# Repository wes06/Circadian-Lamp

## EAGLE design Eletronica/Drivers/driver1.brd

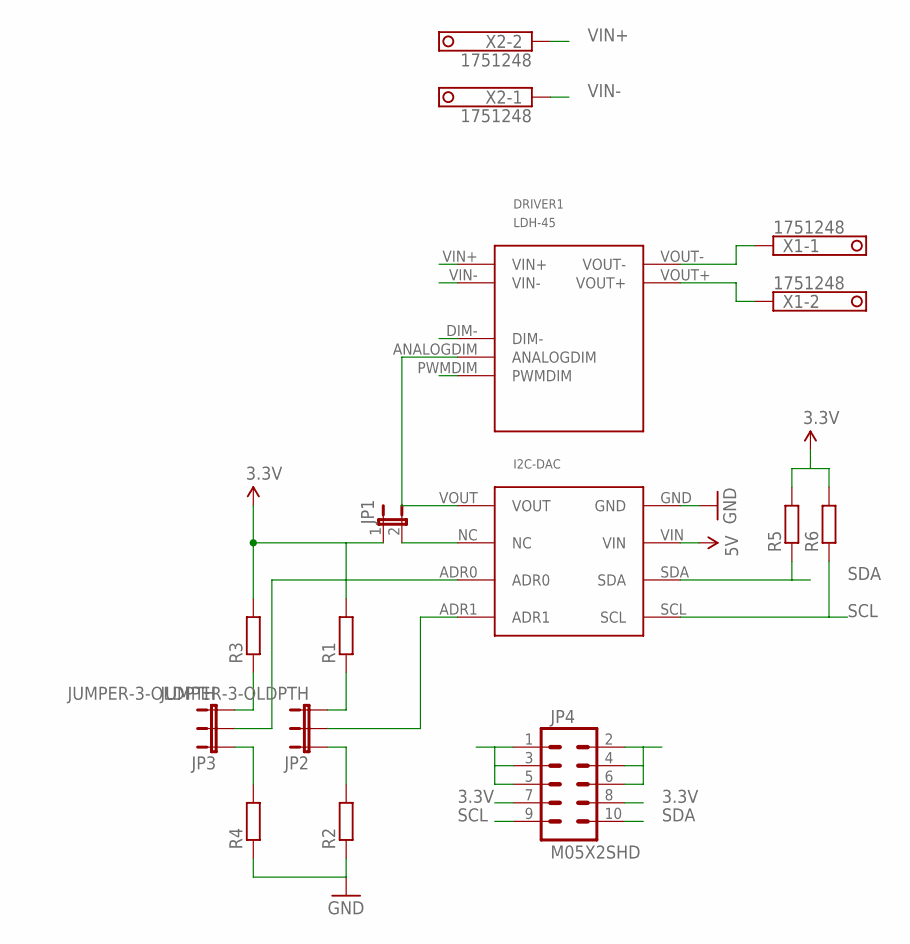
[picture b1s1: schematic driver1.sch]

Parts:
DRIVER1: LDH-45
JP1: JUMPER-2PTH_LOCK; 1X02_LOCK
JP2, JP3: JUMPER-3-OLDPTH; 1X03
JP4: M05X2SHD; 2X5-SHROUDED
R1, R2, R3, R4, R5, R6: R-EU_R0603; R0603
U$1: I2C-DAC
X1, X2: 1751248

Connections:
3.3V: JP1.1, JP4.7, JP4.8, R1.2, R3.2, R5.2, R6.2
5V: JP4.2, JP4.4, JP4.6, U$1.VIN
GND: JP4.1, JP4.3, JP4.5, R2.1, R4.1, U$1.GND
unnamed: DRIVER1.VOUT-, X1.1
unnamed: DRIVER1.VOUT+, X1.2
unnamed: DRIVER1.ANALOGDIM, U$1.VOUT
unnamed: JP3.2, U$1.ADR0
unnamed: JP3.3, R3.1
unnamed: JP1.2, U$1.NC
unnamed: JP3.1, R4.2
unnamed: JP2.3, R1.1
unnamed: JP2.1, R2.2
unnamed: JP2.2, U$1.ADR1
SCL: JP4.9, R6.1, U$1.SCL
SDA: JP4.10, R5.1, U$1.SDA
VIN+: DRIVER1.VIN+, X2.2
VIN-: DRIVER1.VIN-, X2.1

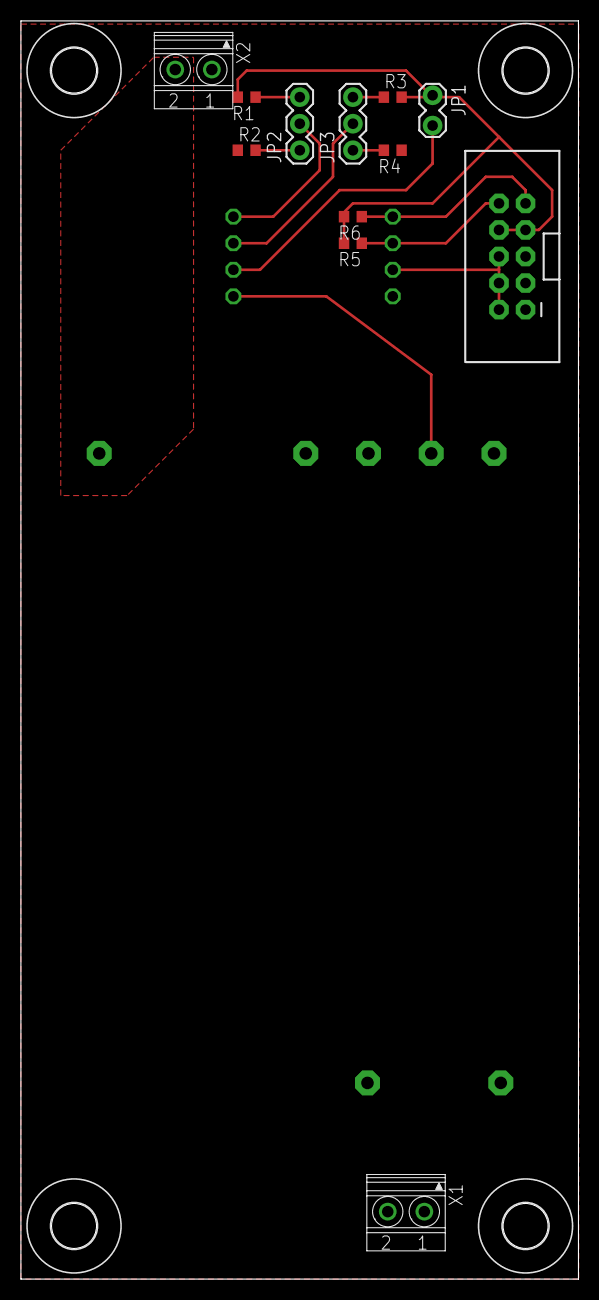
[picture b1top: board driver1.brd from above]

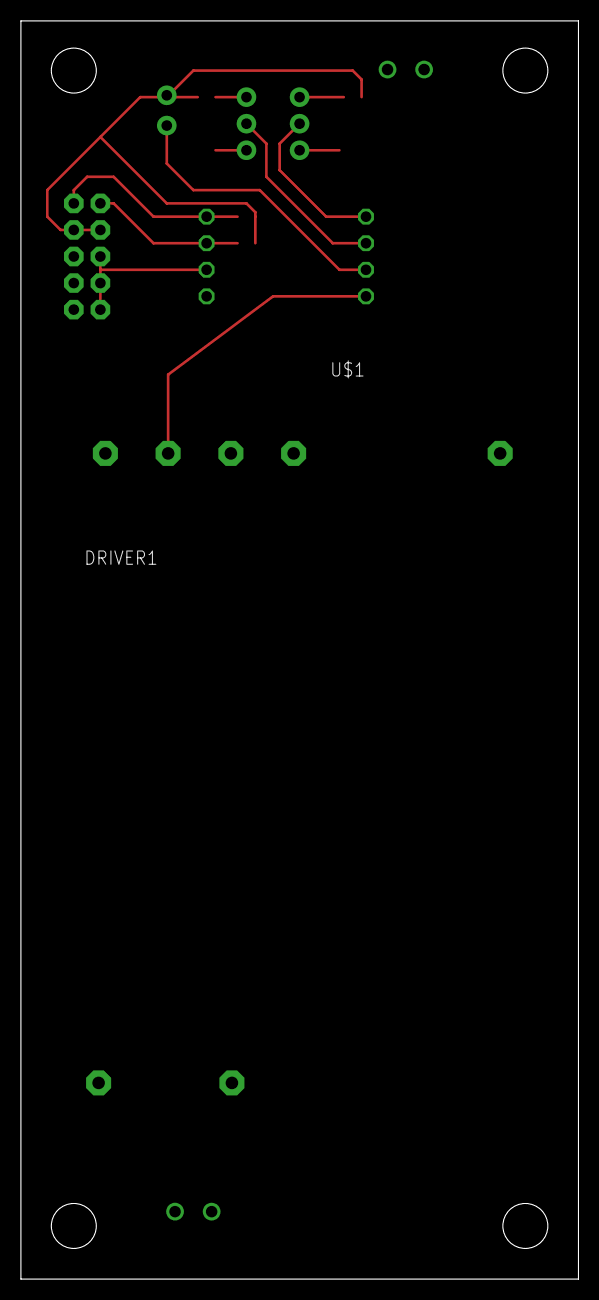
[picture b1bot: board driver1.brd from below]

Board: 2 copper layers, 53.3 x 120.3 mm, 18 parts (2 on the bottom side), 17 nets.

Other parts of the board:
U$2, U$3, U$4, U$5: 4,3

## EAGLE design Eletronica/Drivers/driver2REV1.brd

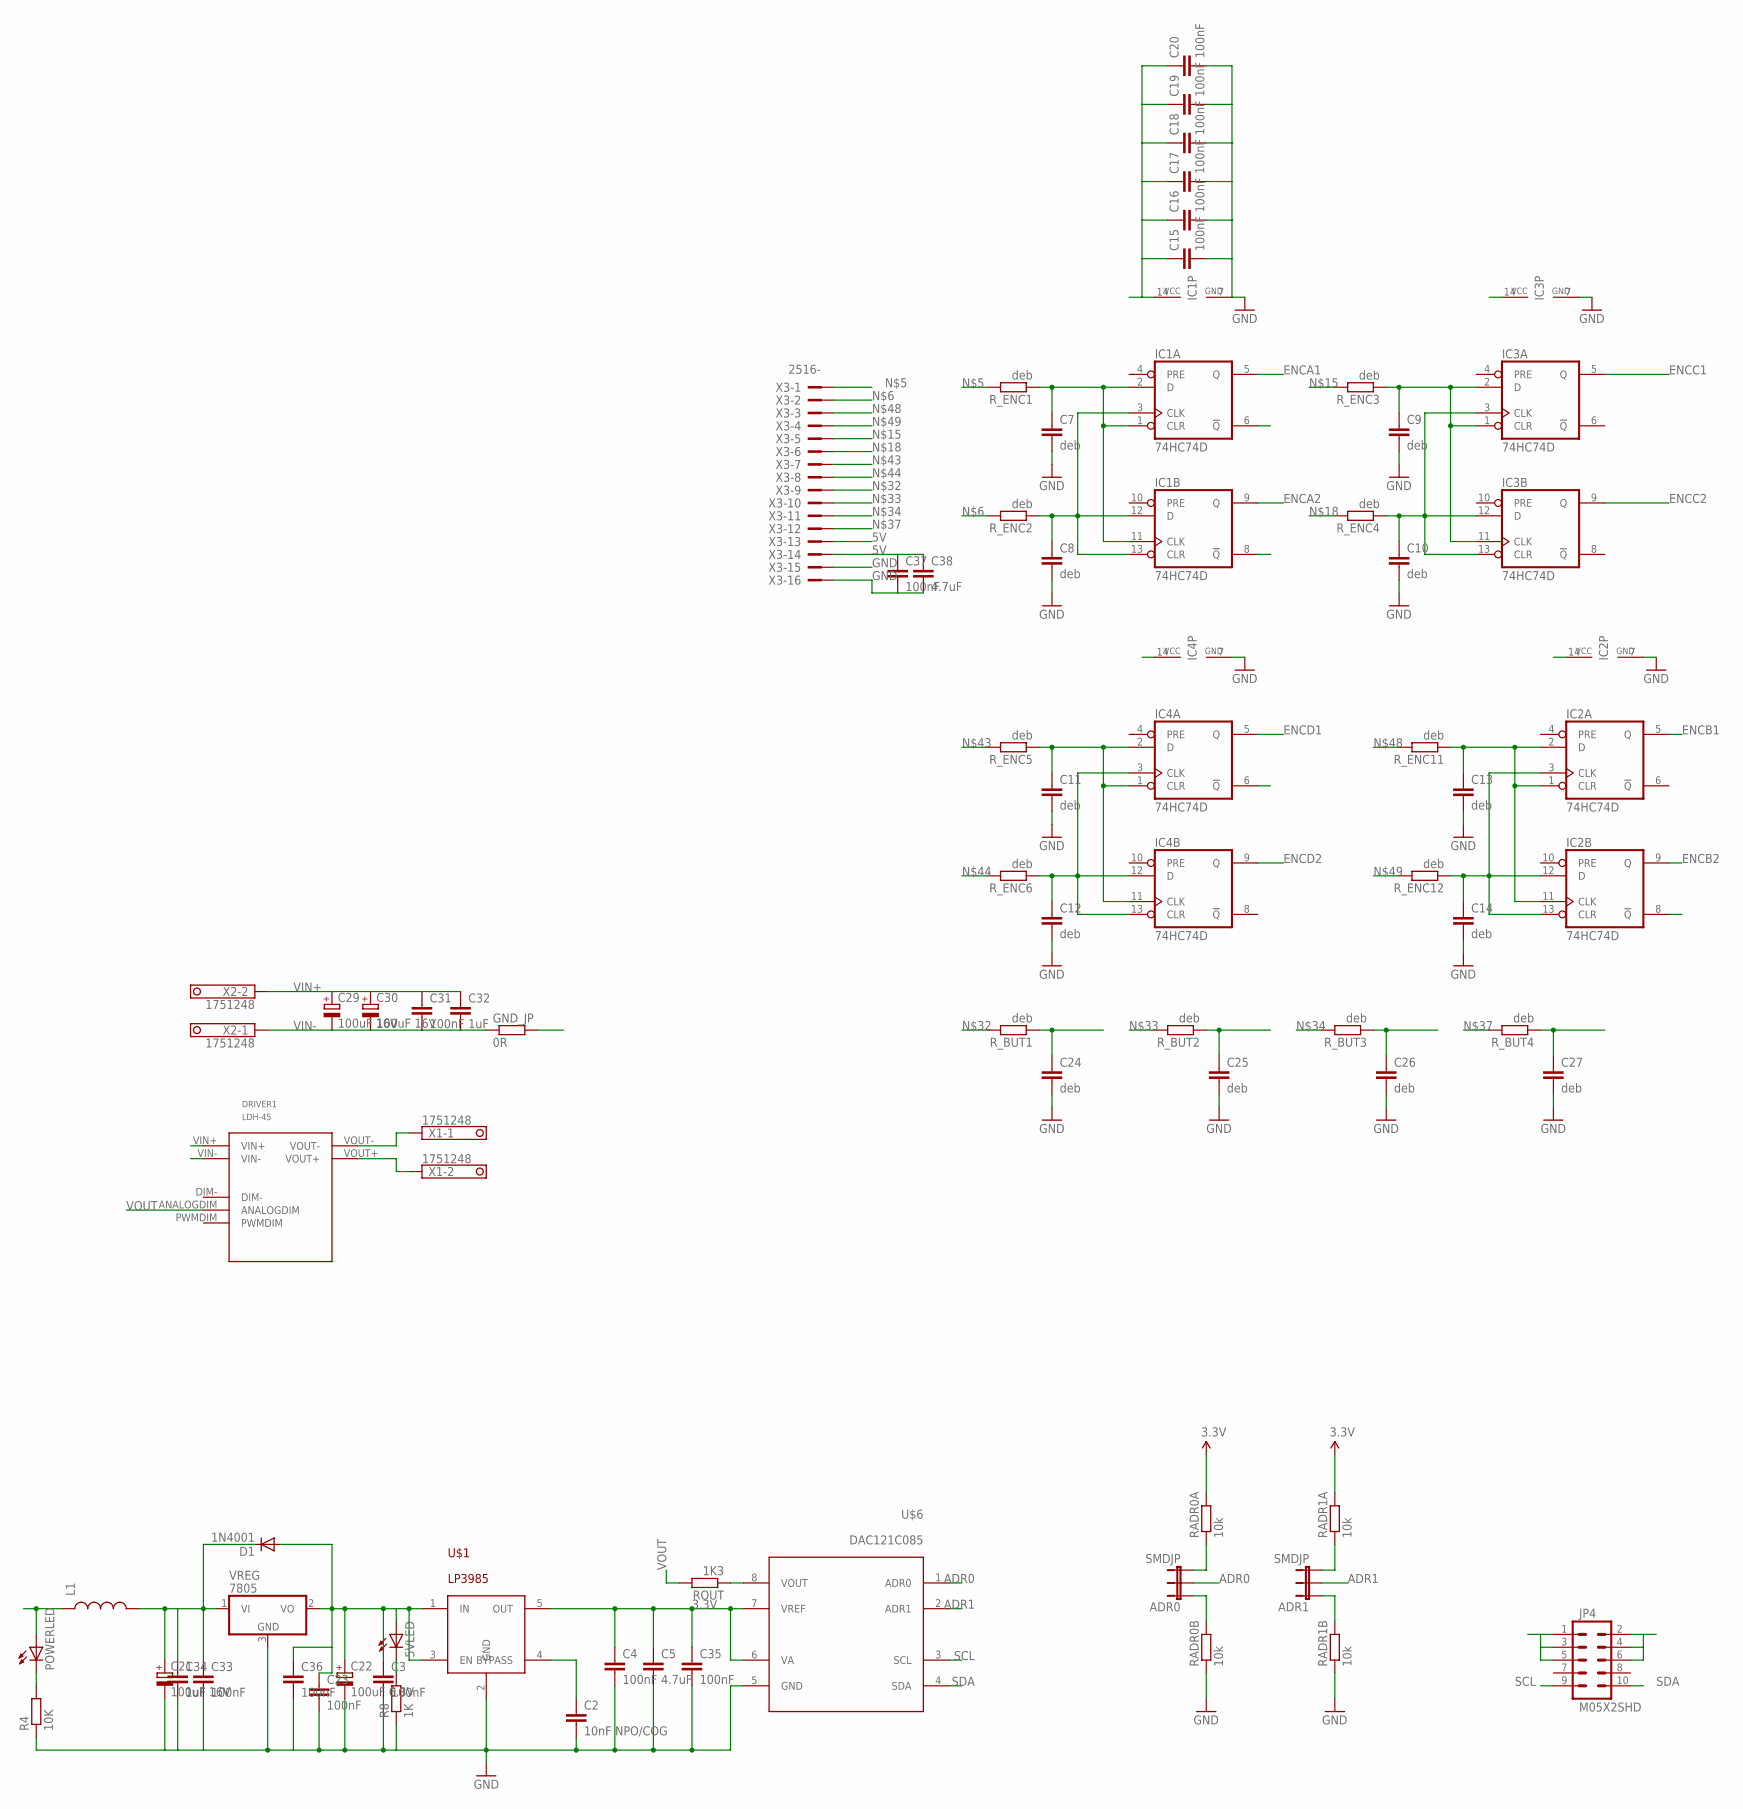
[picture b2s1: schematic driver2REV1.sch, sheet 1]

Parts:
5VLED: LEDCHIP-LED0805; CHIP-LED0805
ADR0, ADR1: SMDJP; SJ_3
C2: 10nF NPO/COG; C0805
C3, C4, C15, C16, C17, C18, C19, C20, C23, C31, C33, C35, C36, C37: 100nF; C0805
C5, C38: 4.7uF; C0805
C7, C8, C9, C10, C11, C12, C13, C14, C24, C25, C26, C27: deb; C0805
C21, C29, C30: 100uF 16V; UD-6,3X5,8_NICHICON
C22: 100uF 6.3V; UD-6,3X5,8_NICHICON
C32, C34: 1uF; C0805
D1: 1N4001; SMB-DIODE
DRIVER1: LDH-45
GND_JP: 0R; R1210
IC1, IC2, IC3, IC4: 74HC74D; SO14
JP4: M05X2SHD; 2X5-SHROUDED
L1: INDUCTOR0805; 0805
POWERLED: LEDCHIP-LED0805; CHIP-LED0805
R4: 10K; R0805
R8: 1K; R0805
RADR0A, RADR0B, RADR1A, RADR1B: 10k; R0603
ROUT: 1K3; R0603
R_BUT1, R_BUT2, R_BUT3, R_BUT4: deb; R0603
R_ENC1, R_ENC2, R_ENC3, R_ENC4, R_ENC5, R_ENC6, R_ENC11, R_ENC12: deb; R0603
U$1: LP3985; SOT23-5
U$6: DAC121C085; VSSOP-8
VREG: 7805; TO252
X1, X2: 1751248
X3: 2516-; PAK100/2500-16

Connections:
3.3V: C4.1, C5.1, C35.1, RADR0A.2, RADR1A.2, U$1.5 (OUT), U$6.6 (VA), U$6.7 (VREF); also elsewhere on the board
5V: 5VLED.A, C3.1, C15.1, C16.1, C17.1, C18.1, C19.1, C20.1, C22.+, C23.1, C36.1, C37.1, C38.1, D1.A, IC1.14 (VCC), IC2.14 (VCC), IC3.14 (VCC), IC4.14 (VCC), JP4.2, JP4.4, JP4.6, U$1.1 (IN), U$1.3 (EN), VREG.2 (VO), X3.13, X3.14; also elsewhere on the board
ADR0: ADR0.2, U$6.1 (ADR0)
ADR1: ADR1.2, U$6.2 (ADR1)
BUTA: C24.1, R_BUT1.1; also elsewhere on the board
BUTB: C25.1, R_BUT2.1; also elsewhere on the board
BUTC: C26.1, R_BUT3.1; also elsewhere on the board
BUTD: C27.1, R_BUT4.1; also elsewhere on the board
ENCA1: IC1.5 (Q); also elsewhere on the board
ENCA2: IC1.9 (Q); also elsewhere on the board
ENCB1: IC2.5 (Q); also elsewhere on the board
ENCB2: IC2.9 (Q); also elsewhere on the board
ENCC1: IC3.5 (Q); also elsewhere on the board
ENCC2: IC3.9 (Q); also elsewhere on the board
ENCD1: IC4.5 (Q); also elsewhere on the board
ENCD2: IC4.9 (Q); also elsewhere on the board
GND: C2.2, C3.2, C4.2, C5.2, C7.2, C8.2, C9.2, C10.2, C11.2, C12.2, C13.2, C14.2, C15.2, C16.2, C17.2, C18.2, C19.2, C20.2, C21.-, C22.-, C23.2, C24.2, C25.2, C26.2, C27.2, C33.2, C34.2, C35.2, C36.2, C37.2, C38.2, GND_JP.2, IC1.7 (GND), IC2.7 (GND), IC3.7 (GND), IC4.7 (GND), JP4.1, JP4.3, JP4.5, R4.1, R8.1, RADR0B.1, RADR1B.1, U$1.2 (GND), U$6.5 (GND), VREG.3 (GND), X3.15, X3.16; also elsewhere on the board
unnamed: DRIVER1.VOUT+, X1.2
unnamed: R_ENC1.2, X3.1
unnamed: R_ENC2.2, X3.2
unnamed: ADR0.3, RADR0A.1
unnamed: ADR0.1, RADR0B.2
unnamed: ADR1.3, RADR1A.1
unnamed: ADR1.1, RADR1B.2
unnamed: C2.1, U$1.4 (BYPASS)
unnamed: C7.1, IC1.1 (CLR), IC1.2 (D), IC1.11 (CLK), R_ENC1.1
unnamed: C8.1, IC1.3 (CLK), IC1.12 (D), IC1.13 (CLR), R_ENC2.1
unnamed: R_ENC3.2, X3.5
unnamed: C21.+, C33.1, C34.1, D1.C, L1.2, VREG.1 (VI)
unnamed: R_ENC4.2, X3.6
unnamed: 5VLED.C, R8.2
unnamed: C9.1, IC3.1 (CLR), IC3.2 (D), IC3.11 (CLK), R_ENC3.1
unnamed: C10.1, IC3.3 (CLK), IC3.12 (D), IC3.13 (CLR), R_ENC4.1
unnamed: C11.1, IC4.1 (CLR), IC4.2 (D), IC4.11 (CLK), R_ENC5.1
unnamed: C12.1, IC4.3 (CLK), IC4.12 (D), IC4.13 (CLR), R_ENC6.1
unnamed: POWERLED.C, R4.2
unnamed: R_BUT1.2, X3.9
unnamed: R_BUT2.2, X3.10
unnamed: R_BUT3.2, X3.11
unnamed: R_BUT4.2, X3.12
unnamed: R_ENC5.2, X3.7
unnamed: R_ENC6.2, X3.8
unnamed: C13.1, IC2.1 (CLR), IC2.2 (D), IC2.11 (CLK), R_ENC11.1
unnamed: C14.1, IC2.3 (CLK), IC2.12 (D), IC2.13 (CLR), R_ENC12.1
unnamed: ROUT.1, U$6.8 (VOUT)
unnamed: R_ENC11.2, X3.3
unnamed: R_ENC12.2, X3.4
SCL: JP4.9, U$6.3 (SCL); also elsewhere on the board
SDA: JP4.10, U$6.4 (SDA); also elsewhere on the board
VIN+: C29.+, C30.+, C31.1, C32.1, DRIVER1.VIN+, L1.1, POWERLED.A, X2.2
VIN-: C29.-, C30.-, C31.2, C32.2, DRIVER1.VIN-, GND_JP.1, X2.1
VOUT: DRIVER1.ANALOGDIM, ROUT.2
VOUT-: DRIVER1.VOUT-, X1.1

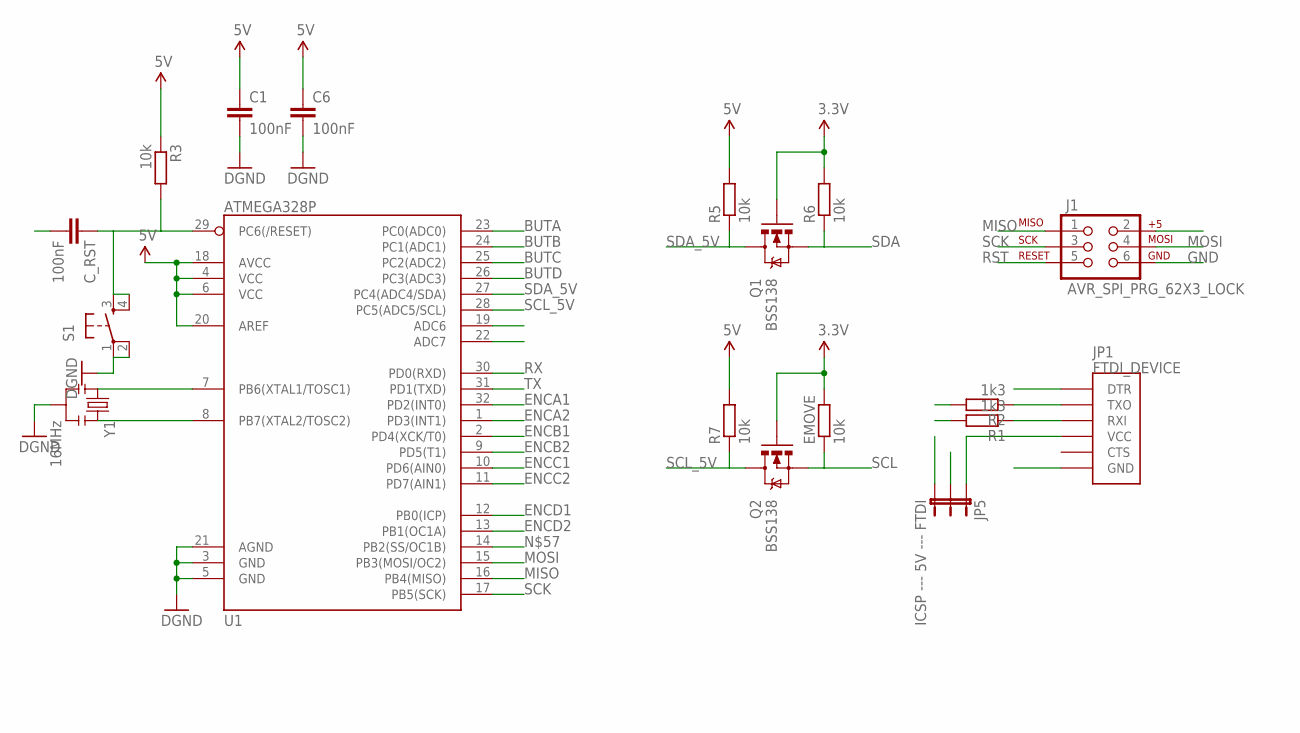
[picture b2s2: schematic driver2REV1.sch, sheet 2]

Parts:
C1, C6: 100nF; C0805
C_RST: 100nF; C0805
EMOVE: 10k; R0603
J1: AVR_SPI_PRG_62X3_LOCK; 2X3_LOCK
JP1: FTDI_DEVICE; FTDI_DEVICE_SIDE
JP5: ICSP --- 5V --- FTDI; SJ_3
Q1, Q2: BSS138; SOT23
R1, R2: 1k3; R0603
R3, R5, R6, R7: 10k; R0603
S1: TAC_SWITCHSMD; TACTILE_SWITCH_SMD
U1: ATMEGA328P; TQFP32-08
Y1: 16MHz; RESONATOR-SMD

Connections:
3.3V: EMOVE.2, Q1.1 (G), Q2.1 (G), R6.2; also elsewhere on the board
5V: C1.1, C6.1, JP5.2, R3.1, R5.2, R7.2, U1.4 (VCC), U1.6 (VCC), U1.18 (AVCC), U1.20 (AREF); also elsewhere on the board
BUTA: U1.23 (PC0(ADC0)); also elsewhere on the board
BUTB: U1.24 (PC1(ADC1)); also elsewhere on the board
BUTC: U1.25 (PC2(ADC2)); also elsewhere on the board
BUTD: U1.26 (PC3(ADC3)); also elsewhere on the board
ENCA1: U1.32 (PD2(INT0)); also elsewhere on the board
ENCA2: U1.1 (PD3(INT1)); also elsewhere on the board
ENCB1: U1.2 (PD4(XCK/T0)); also elsewhere on the board
ENCB2: U1.9 (PD5(T1)); also elsewhere on the board
ENCC1: U1.10 (PD6(AIN0)); also elsewhere on the board
ENCC2: U1.11 (PD7(AIN1)); also elsewhere on the board
ENCD1: U1.12 (PB0(ICP)); also elsewhere on the board
ENCD2: U1.13 (PB1(OC1A)); also elsewhere on the board
FTDI_RST: C_RST.2, JP1.P$1 (DTR)
GND: C1.2, C6.2, J1.6, JP1.P$6 (GND), S1.1, S1.2, U1.3 (GND), U1.5 (GND), U1.21 (AGND), Y1.2; also elsewhere on the board
ISP_5V: J1.2, JP5.3
MISO: J1.1, U1.16 (PB4(MISO))
MOSI: J1.4, U1.15 (PB3(MOSI/OC2))
unnamed: U1.7 (PB6(XTAL1/TOSC1)), Y1.1
unnamed: U1.8 (PB7(XTAL2/TOSC2)), Y1.3
unnamed: JP1.P$2 (TXO), R2.1
unnamed: JP1.P$3 (RXI), R1.1
unnamed: JP1.P$4 (VCC), JP5.1
RST: C_RST.1, J1.5, R3.2, S1.3, S1.4, U1.29 (PC6(/RESET))
RX: R1.2, U1.30 (PD0(RXD))
SCK: J1.3, U1.17 (PB5(SCK))
SCL: EMOVE.1, Q2.2 (S); also elsewhere on the board
SCL_5V: Q2.3 (D), R7.1, U1.28 (PC5(ADC5/SCL))
SDA: Q1.2 (S), R6.1; also elsewhere on the board
SDA_5V: Q1.3 (D), R5.1, U1.27 (PC4(ADC4/SDA))
TX: R2.2, U1.31 (PD1(TXD))

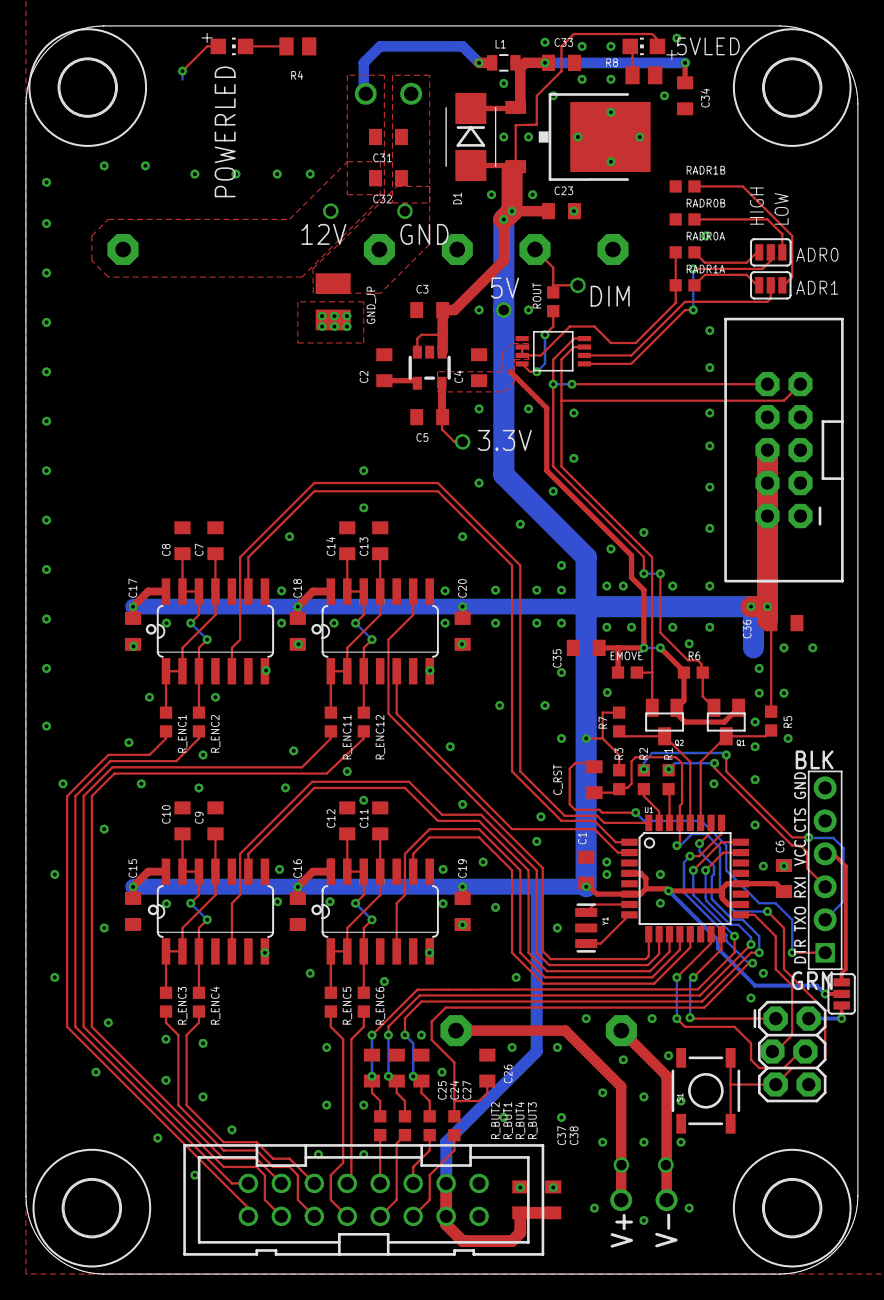
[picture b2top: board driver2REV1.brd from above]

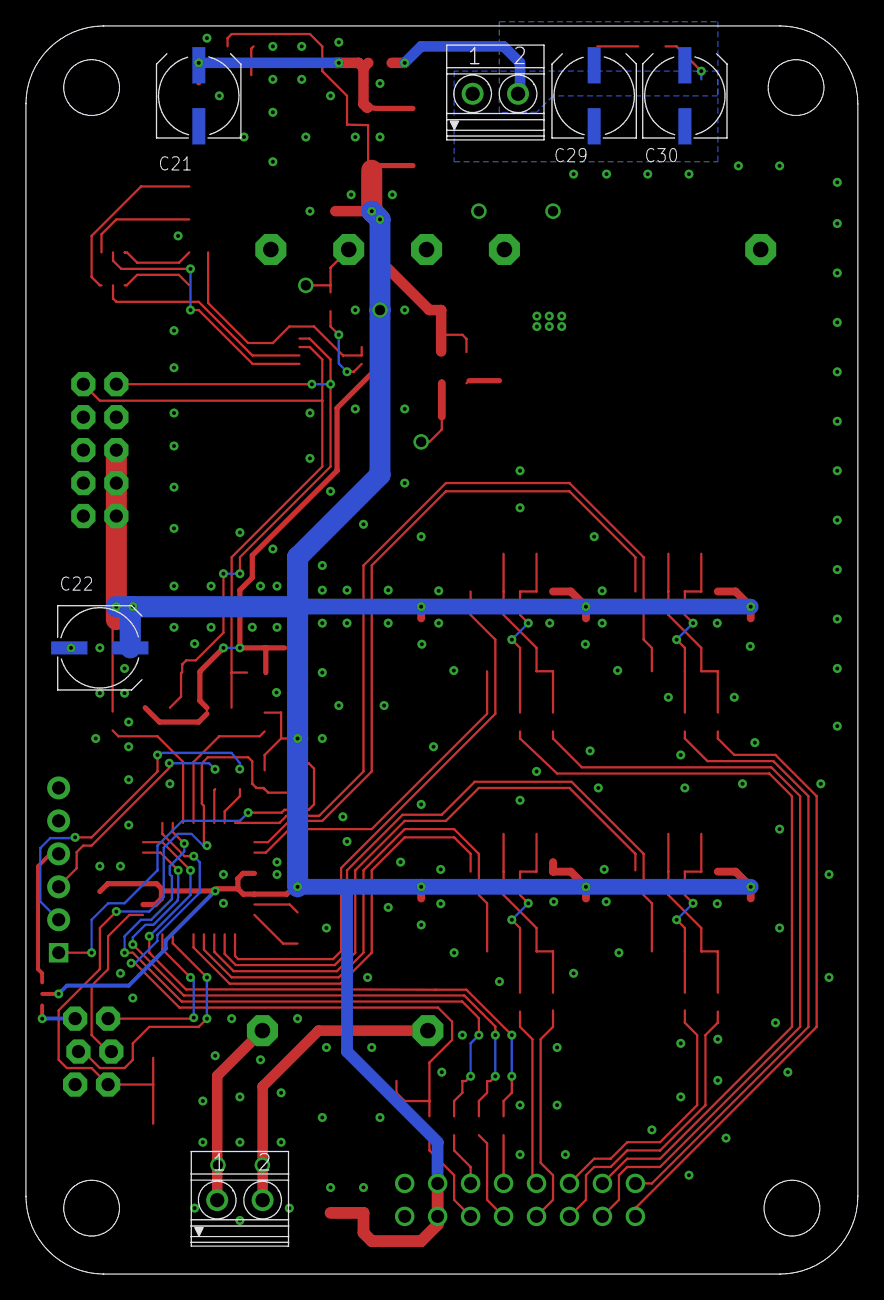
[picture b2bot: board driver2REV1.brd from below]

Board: 2 copper layers, 64.1 x 96.2 mm, 95 parts (7 on the bottom side), 68 nets.

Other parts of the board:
U$2, U$3, U$4, U$5: 4,3

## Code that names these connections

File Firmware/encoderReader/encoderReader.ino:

//     A0 - PC0 - BUTA
//     A1 - PC1 - BUTB
//     A2 - PC2 - BUTC
//     A3 - PC3 - BUTD
//      - 
//     D2 - PD2 - ENCA1
//     D3 - PD3 - ENCA2
//     D4 - PD4 - ENCB1
//     D5 - PD5 - ENCB2
//     D6 - PD6 - ENCC1
//     D7 - PD7 - ENCC2
//     D8 - PB0 - ENCD1
//     D9 - PB1 - ENCD2

const int BUTA = A0;
const int BUTB = A1;
const int BUTC = A2;
const int BUTD = A3;

const int ENCA1 = 2;
const int ENCA2 = 3;
const int ENCB1 = 4;
const int ENCB2 = 5;
const int ENCC1 = 6;
const int ENCC2 = 7;
const int ENCD1 = 8;
const int ENCD2 = 9;

int encState[8] = {0,0,0,0,0,0,0,0};
int encDeb[8] = {100,100,100,100,100,100,100,100}; //debounce < duracao do pulso em millis
int encDel[8] = {100,100,100,100,100,100,100,100}; //del > duracao do pulso em millis
int encLast[8] = {0,0,0,0,0,0,0,0};

int encVal[8] = {};

int knobMode = 0; 	//0 = raw(cada encoder controla 1 grupo de led
					//1 = grupos, encoder A = todos os LEDs, B = Frios

float offVtg = 0.25;
float onVtg = 1.3;
float refVtg = 3.3;

byte offByte;
byte onByte;
int encConstraints = 1000;


void setup(){

	Wire.begin();

	//pinMode(2, INPUT);
    //pinMode(3, INPUT);
    //pinMode(4, INPUT);
    //pinMode(5, INPUT);
    //pinMode(6, INPUT);
    //pinMode(7, INPUT);
    DDRD &= 0b11111011;
	//DDRD &= ~(1 << PD2);
	//DDRD &= ~(1 << PD3);
	//DDRD &= ~(1 << PD4);
	//DDRD &= ~(1 << PD5);
	//DDRD &= ~(1 << PD6);

    //pinMode(8, INPUT);
    //pinMode(9, INPUT);
	DDRB &= ~(1 << PB0);
	DDRB &= ~(1 << PB1);

	//pinMode(BUTA ,INPUT);
	//pinMode(BUTB ,INPUT);
	//pinMode(BUTC ,INPUT);
	//pinMode(BUTD ,INPUT);
	DDRC &= ~(1 << PC0);
	DDRC &= ~(1 << PC1);
	DDRC &= ~(1 << PC2);
	DDRC &= ~(1 << PC3);


	offByte = (offVtg/refVtg) * 4096;
	onByte = (onVtg/refVtg) * 4096;

}

void loop(){

	//1001000 broadcast address

	//0x0C	#12	0001100	ADR1 NC		ADR0 NC
	//0x0D	#13 0001101	ADR1 NC		ADR0 GND
	//0x0E	#14	0001110	ADR1 NC		ADR0 VA
	//0x08	#8	0001000	ADR1 GND	ADR0 NC

	Wire.beginTransmission(12);		// transmit to device
	Wire.write("0000" + string(4096,BIN));

	Wire.write(byte(0x00));			// 
	Wire.write(byte(0x00));			// 
	Wire.endTransmission();

	Wire.beginTransmission(13);		// transmit to device
	Wire.write(byte(0x00));			// 
	Wire.write(byte(0x00));			// 
	Wire.endTransmission();

	Wire.beginTransmission(14);		// transmit to device
	Wire.write(byte(0x00));			// 
	Wire.write(byte(0x00));			// 
	Wire.endTransmission();

	Wire.beginTransmission(8);		// transmit to device
	Wire.write(byte(0x00));			// 
	Wire.write(byte(0x00));			// 
	Wire.endTransmission();

/*
For a write operation, the master follows the ACK by sending the upper eight data bits to the DAC121C081. Then the DAC121C081 ACKs the transfer by driving SDA low. Next, the lower eight data bits are sent by the master. The DAC121C081 then ACKs the transfer. At this point, the DAC output updates to reflect the contents of the 16-bit DAC register. Next, the master either sends another pair of data bytes, generates a Stop condition to end communication, or generates a Repeated Start condition to communicate with another device on the bus.
*/

	encState[0] = (PIND & (1<<PD2));    //Read the PORTD pin 2 value and put it in the variable
	encState[1] = (PIND & (1<<PD3));
	encState[2] = (PIND & (1<<PD4));
	encState[3] = (PIND & (1<<PD5));
	encState[4] = (PIND & (1<<PD6));
	encState[5] = (PIND & (1<<PD7));
	encState[6] = (PINB & (1<<PB0));
	encState[7] = (PINB & (1<<PB1));

	for(int i =0;i<8;i++){
		if(encState[i] && encLast[i] - millis() > encDel[i]){
			encLast[i] = millis();
			encTrig == false;
		}

		if(encState[i] && encLast[i] - millis() > endDeb[i] && encTrig == false){
			encTrig[i] == true;
		}


	}


	if(knobMode == 0){
		if(encTrig[0]) encVal[0]++;
		if(encTrig[1]) encVal[1]--;
		if(encTrig[2]) encVal[2]++;
		if(encTrig[3]) encVal[3]--;
		if(encTrig[4]) encVal[4]++;
		if(encTrig[5]) encVal[5]--;
		if(encTrig[6]) encVal[6]++;
		if(encTrig[7]) encVal[7]--;

		for(int i =0;i<8;i++){
			encVal[i] = constrain(encVal, -1*encConstraints, encConstraints)
			encTrig[i] = false;
		}
	}
	else if(knobMode == 1){

	}

}

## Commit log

2016-08-29 Reorganization
2016-09-02 Mechanical and Electronics files added
2016-09-02 Organizing
2016-09-06 Deleted deprecated
2016-09-09 Color temp vs daytime calculating draft
2016-09-09 Re-organizing
2016-09-09 Ping for iPhone draft

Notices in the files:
parts and their libraries:
SparkFun-Passives: Licensing: CC v3.0 Share-Alike You are welcome to use this library for commercial purposes.
